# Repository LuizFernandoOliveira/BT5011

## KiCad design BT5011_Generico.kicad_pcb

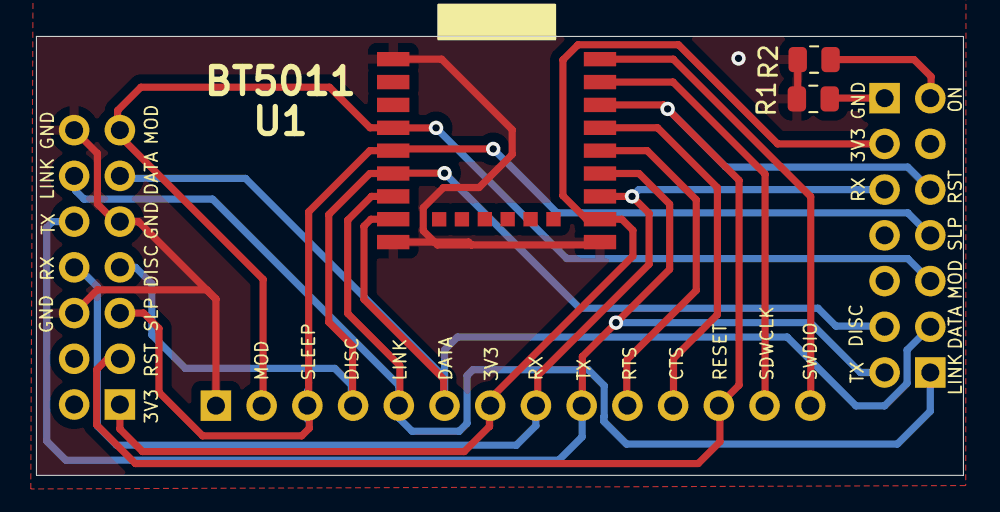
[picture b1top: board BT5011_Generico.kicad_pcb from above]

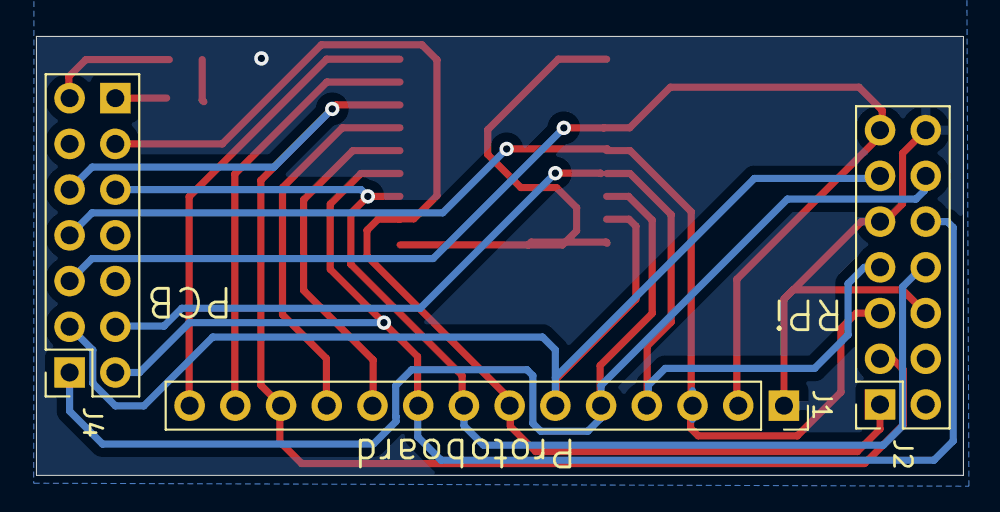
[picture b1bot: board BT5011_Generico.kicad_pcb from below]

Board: 2 copper layers, 51.5 x 24.4 mm, 6 parts (3 on the bottom side), 16 nets.

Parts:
J1: Conn_01x14; PinSocket_1x14_P2.54mm_Vertical
J2, J4: Conn_02x07_Odd_Even; PinSocket_2x07_P2.54mm_Vertical
R1, R2: R; R_0805_2012Metric
U1: E104-BT5011-Lib_sch; E104-BT5011

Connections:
+3V3: J1.7, J2.1, J4.12, U1.17
CTS: J1.11, U1.21
DATA: J1.6, J2.11, J4.3, U1.8
DISC: J1.4, J2.7, J4.4, U1.6
GND: J1.1, J2.6, J2.9, J2.14, R1.1, R2.1, U1.1, U1.9, U1.16
LINK: J1.5, J2.12, J4.1, U1.7
MOD: J1.2, J2.13, J4.5, U1.4
Pad13: J4.13, R2.2
Pad14: J4.14, R1.2
RESET: J1.12, J2.3, J4.9, U1.22
RTS: J1.10, U1.20
RX: J1.8, J2.8, J4.10, U1.18
SDWCLK: J1.13, U1.23
SLEEP: J1.3, J2.5, J4.7, U1.5
SWDIO: J1.14, U1.24
TX: J1.9, J2.10, J4.2, U1.19

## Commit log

2024-01-28 Initial version
